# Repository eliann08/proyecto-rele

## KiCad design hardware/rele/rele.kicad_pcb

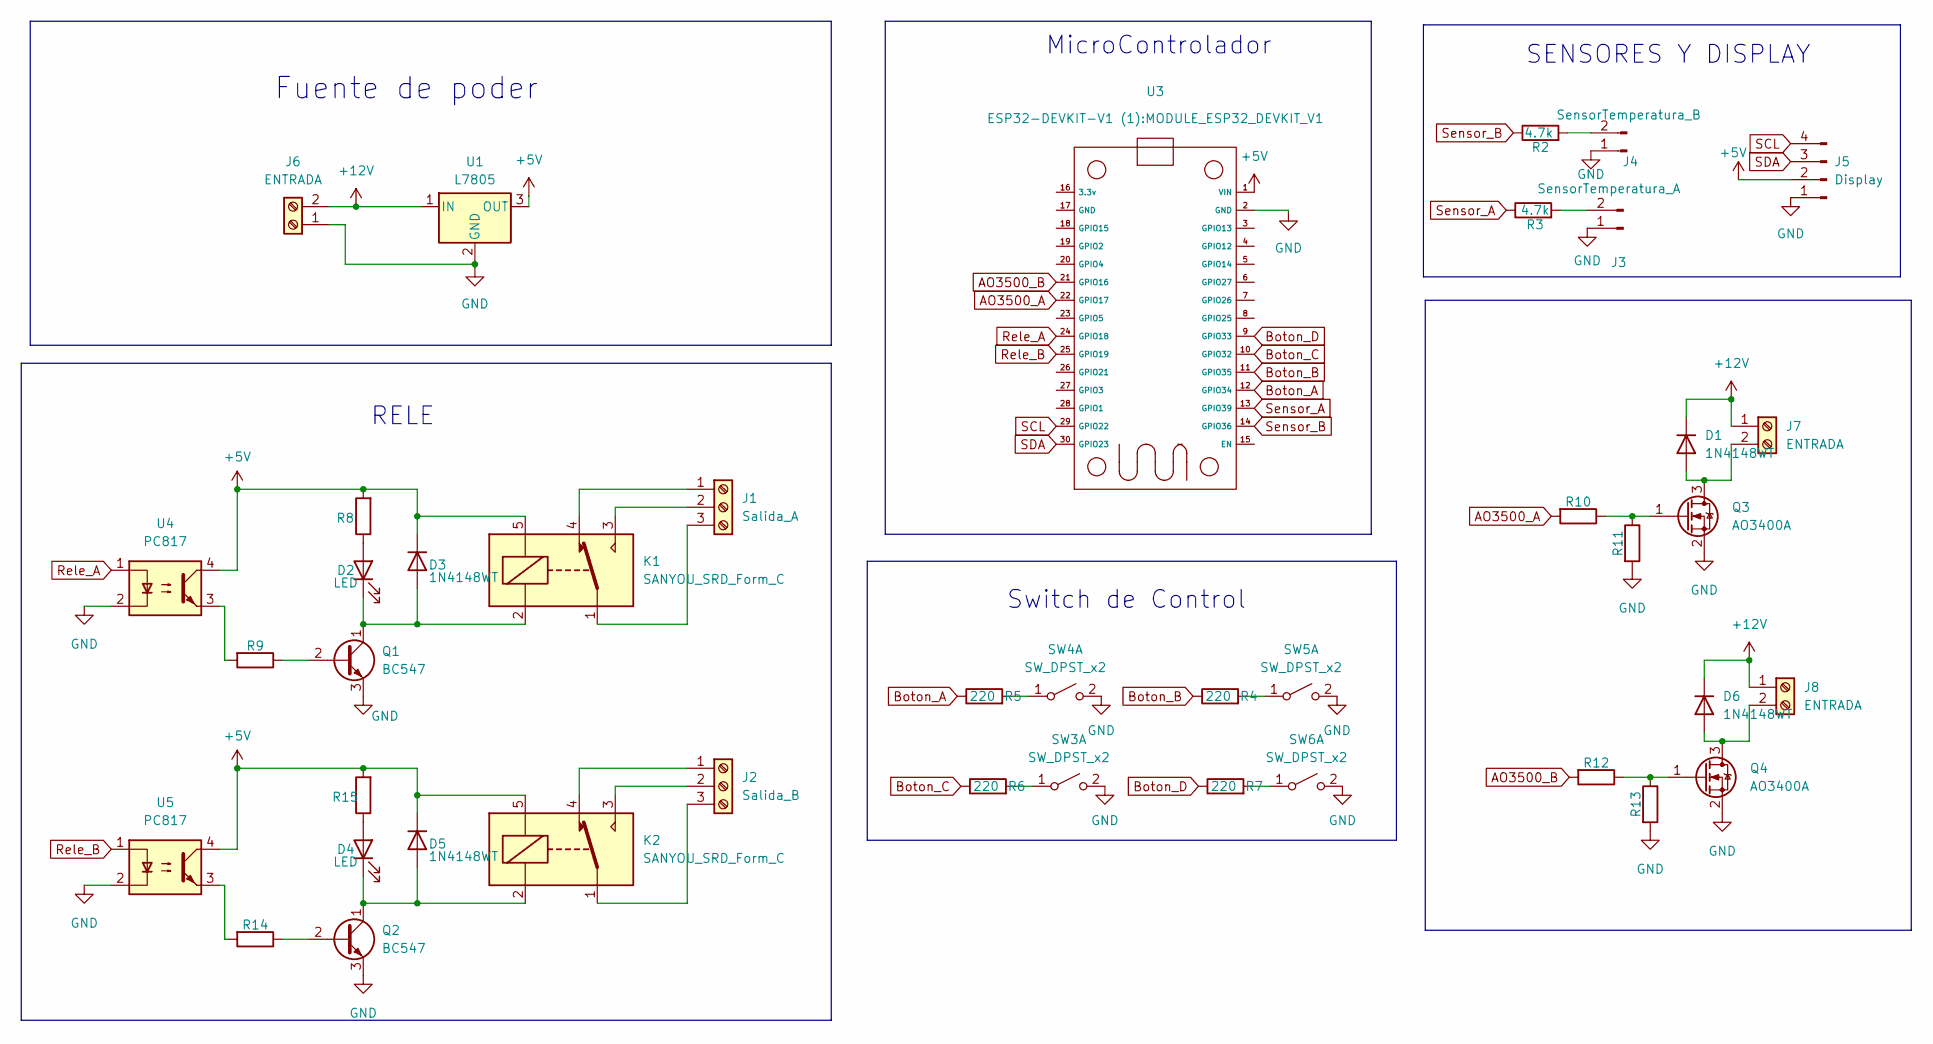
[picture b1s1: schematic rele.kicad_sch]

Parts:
D1, D3, D5, D6: 1N4148WT; D_A-405_P10.16mm_Horizontal
D2, D4: LED; LED_D5.0mm
J1: Salida_A; TerminalBlock_MaiXu_MX126-5.0-03P_1x03_P5.00mm
J2: Salida_B; TerminalBlock_MaiXu_MX126-5.0-03P_1x03_P5.00mm
J3: SensorTemperatura_A; PinHeader_1x02_P2.54mm_Vertical
J4: SensorTemperatura_B; PinHeader_1x02_P2.54mm_Vertical
J5: Display; PinHeader_1x04_P2.54mm_Vertical
J6, J7, J8: ENTRADA; TerminalBlock_Phoenix_MKDS-1,5-2-5.08_1x02_P5.08mm_Horizont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
K1, K2: SANYOU_SRD_Form_C; Relay_SPDT_SANYOU_SRD_Series_Form_C
Q1, Q2: BC547; TO-92_Inline
Q3, Q4: AO3400A; SOT-23
R2, R3: 4.7k; R_0805_2012Metric_Pad1.20x1.40mm_HandSolder
R4, R5, R6, R7: 220; R_0805_2012Metric_Pad1.20x1.40mm_HandSolder
R8, R9, R10, R11, R12, R13, R14, R15: R_0805_2012Metric_Pad1.20x1.40mm_HandSolder
SW3, SW4, SW5, SW6: SW_DPST_x2; SW_PUSH_6mm
U1: L7805; TO-220-3_Vertical
U3: MODULE_ESP32_DEVKIT_V1
U4, U5: PC817; DIP-4_W7.62mm

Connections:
+5V: D3.1 (K), D5.1 (K), J5.2, K1.5, K2.5, R8.2, R15.2, U1.3 (OUT), U3.1 (VIN), U4.4, U5.4
+12V: D1.1 (K), D6.1 (K), J6.2, J7.1, J8.1, U1.1 (IN)
AO3500_A: R10.2, U3.22 (GPIO17)
AO3500_B: R12.2, U3.21 (GPIO16)
Boton_A: R5.1, U3.12 (GPIO34)
Boton_B: R4.1, U3.11 (GPIO35)
Boton_C: R6.1, U3.10 (GPIO32)
Boton_D: R7.1, U3.9 (GPIO33)
GND: J3.1, J4.1, J5.1, J6.1, Q1.3 (E), Q2.3 (E), Q3.2 (S), Q4.2 (S), R11.2, R13.2, SW3.2 (B), SW4.2 (B), SW5.2 (B), SW6.2 (B), U1.2 (GND), U1.e (GND), U3.2 (GND), U4.2, U5.2
unnamed: D1.2 (A), J7.2, Q3.3 (D)
unnamed: D2.2 (A), R8.1
unnamed: D2.1 (K), D3.2 (A), K1.2, Q1.1 (C)
unnamed: D4.2 (A), R15.1
unnamed: D4.1 (K), D5.2 (A), K2.2, Q2.1 (C)
unnamed: D6.2 (A), J8.2, Q4.3 (D)
unnamed: J1.1, K1.4
unnamed: J1.2, K1.3
unnamed: J1.3, K1.1
unnamed: J2.1, K2.4
unnamed: J2.2, K2.3
unnamed: J2.3, K2.1
unnamed: J3.2, R3.2
unnamed: J4.2, R2.2
unnamed: Q1.2 (B), R9.1
unnamed: Q2.2 (B), R14.1
unnamed: Q3.1 (G), R10.1, R11.1
unnamed: Q4.1 (G), R12.1, R13.1
unnamed: R9.2, U4.3
unnamed: R14.2, U5.3
unnamed: R6.2, SW3.1 (A)
unnamed: R5.2, SW4.1 (A)
unnamed: R4.2, SW5.1 (A)
unnamed: R7.2, SW6.1 (A)
Rele_A: U3.24 (GPIO18), U4.1
Rele_B: U3.25 (GPIO19), U5.1
SCL: J5.4, U3.29 (GPIO22)
SDA: J5.3, U3.30 (GPIO23)
Sensor_A: R3.1, U3.13 (GPIO39)
Sensor_B: R2.1, U3.14 (GPIO36)

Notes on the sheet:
Fuente de poder
RELE
MicroControlador
Switch de Control
SENSORES Y DISPLAY

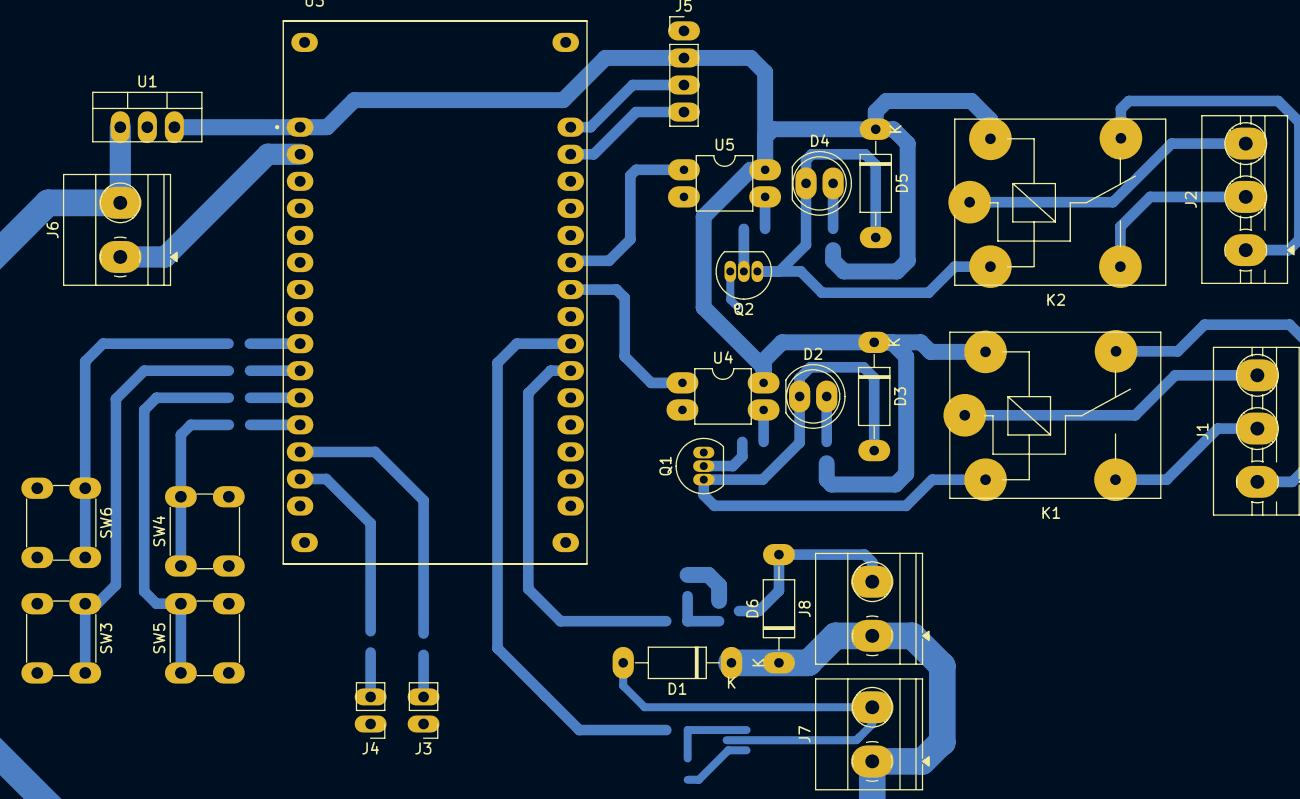
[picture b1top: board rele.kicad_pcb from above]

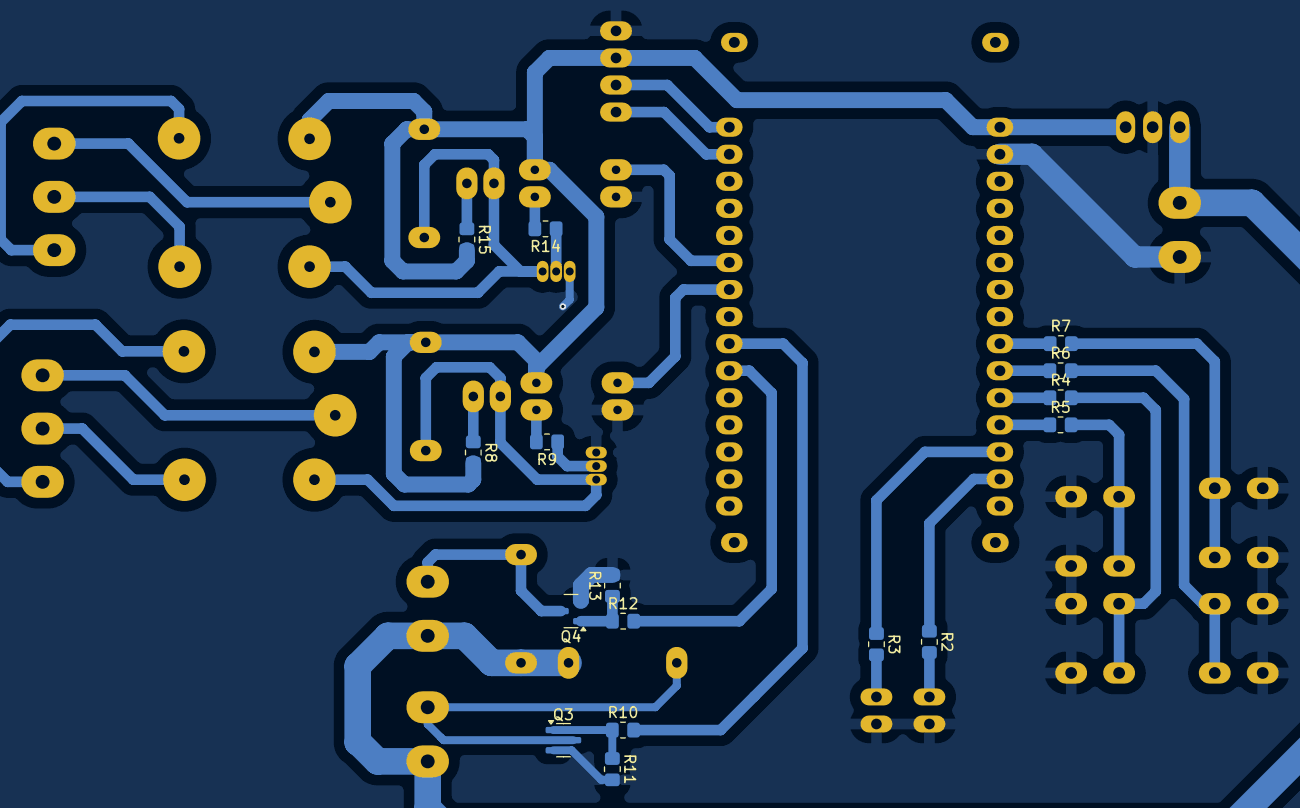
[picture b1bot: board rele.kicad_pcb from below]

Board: 2 copper layers, 42 parts (16 on the bottom side), 39 nets.
